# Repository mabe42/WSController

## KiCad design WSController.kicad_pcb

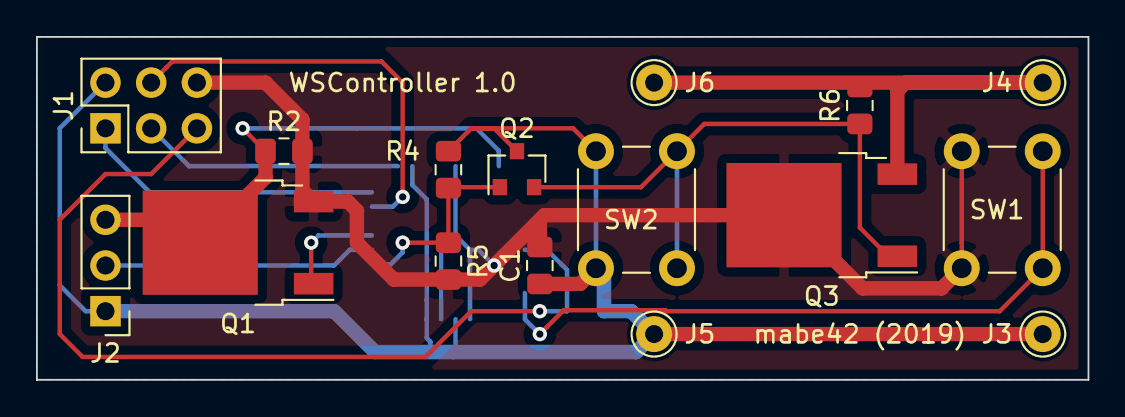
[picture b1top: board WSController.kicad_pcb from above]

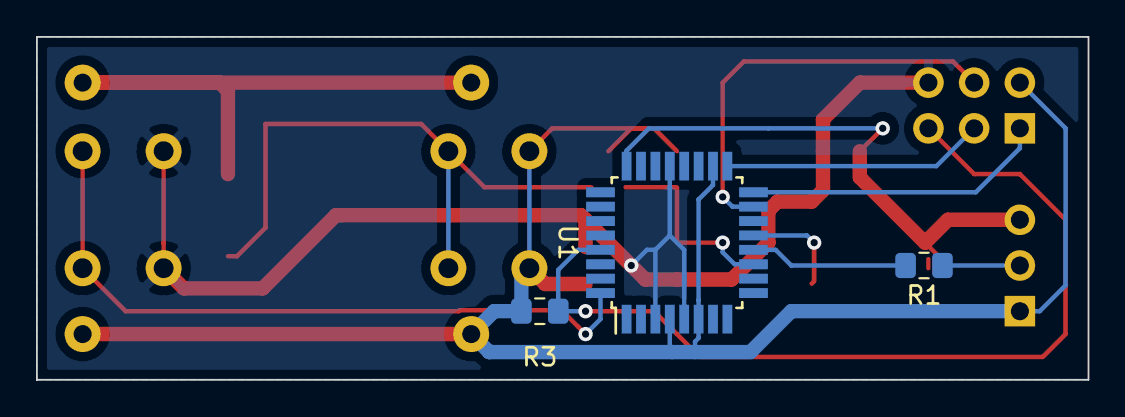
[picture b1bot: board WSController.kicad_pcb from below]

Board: 2 copper layers, 58.4 x 19.1 mm, 19 parts (3 on the bottom side), 14 nets.

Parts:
C1: 0.1uF; C_0805_2012Metric_Pad1.15x1.40mm_HandSolder
J1: AVR-ISP-6; PinHeader_2x03_P2.54mm_Vertical
J2: LED Strip; PinHeader_1x03_P2.54mm_Vertical
J3: Li+; Pin_D1.0mm_L10.0mm
J4: Li-; Pin_D1.0mm_L10.0mm
J5: Charger+; Pin_D1.0mm_L10.0mm
J6: Charger-; Pin_D1.0mm_L10.0mm
Q1, Q3: IRLU024N; TO-252-2
Q2: BC857; SOT-23
R1: 470; R_0805_2012Metric_Pad1.15x1.40mm_HandSolder
R2, R6: 10; R_0805_2012Metric_Pad1.15x1.40mm_HandSolder
R3, R4: 10k; R_0805_2012Metric_Pad1.15x1.40mm_HandSolder
R5: 1k; R_0805_2012Metric_Pad1.15x1.40mm_HandSolder
SW1: Switch Mode; SW_PUSH_6mm
SW2: Switch ON; SW_PUSH_6mm
U1: ATmega328P-AU; TQFP-32_7x7mm_P0.8mm

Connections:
GND: C1.2, J1.6, Q1.3, Q3.2, R2.2, R5.2, SW1.2, U1.3, U1.5, U1.21
GNDPWR: J4.1, J6.1, Q3.3, R6.2
LED_GND: J2.3, Q1.2, R2.1, U1.24
LED_VCC: C1.1, J1.2, J2.1, J3.1, J5.1, Q2.3, R3.1, R4.1, SW2.2, U1.4, U1.6, U1.18
LED_data: J2.2, R1.1
MISO: J1.1, U1.16
MOSI: J1.4, U1.15
unnamed: Q2.2, Q3.1, R6.1, SW2.1
unnamed: R1.2, U1.12
SCK: J1.3, U1.17
keep_power: Q2.1, R4.2, R5.1, U1.11
mode: SW1.1, U1.32
reset: J1.5, R3.2, U1.29
shunt: Q1.1, U1.13

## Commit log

2019-11-24 first commit - no further details
2019-11-24 deleted unnecessary file PCB-old.png
2019-11-27 corrected values of R4 and R5
